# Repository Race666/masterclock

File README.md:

# Mutteruhrsteuerung

Firmware und Schaltungen zum Steuern von sog. Nebenuhren (z.B. Bahnhofsuhren)

Dokumentation und Details auf [albert-hetzles.de](http://albert-hetzles.de/mutteruhr/index.shtml)

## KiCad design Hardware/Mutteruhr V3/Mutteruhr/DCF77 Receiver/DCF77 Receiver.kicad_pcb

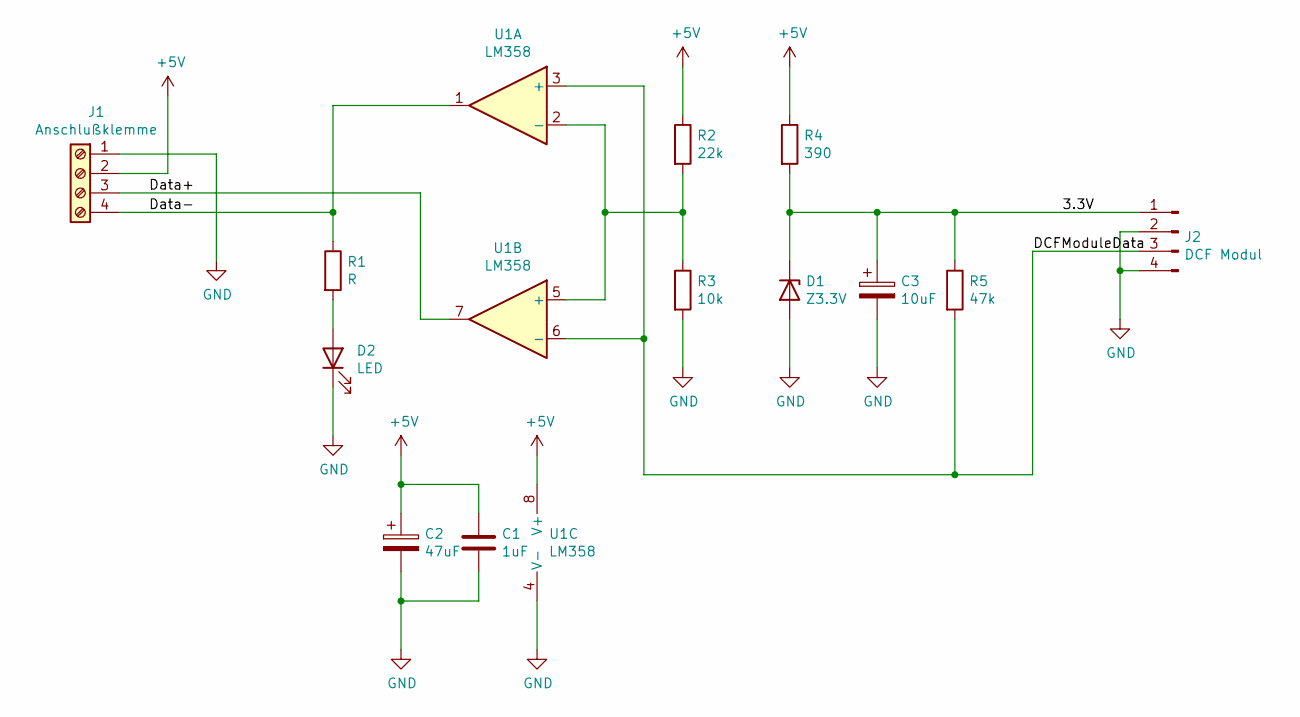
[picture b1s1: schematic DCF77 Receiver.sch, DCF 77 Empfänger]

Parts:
C1: 1uF; C_Rect_L7.0mm_W3.5mm_P5.00mm
C2: 47uF; CP_Radial_D6.3mm_P2.50mm
C3: 10uF; CP_Radial_D6.3mm_P2.50mm
D1: Z3.3V; D_DO-35_SOD27_P10.16mm_Horizontal
D2: LED; LED_D3.0mm
J1: Anschlußklemme; TerminalBlock_Phoenix_MKDS-3-4-5.08_1x04_P5.08mm_Horizontal
J2: DCF Modul; PinHeader_1x04_P2.54mm_Vertical
R1: R; R_Axial_DIN0207_L6.3mm_D2.5mm_P10.16mm_Horizontal
R2: 22k; R_Axial_DIN0207_L6.3mm_D2.5mm_P10.16mm_Horizontal
R3: 10k; R_Axial_DIN0207_L6.3mm_D2.5mm_P10.16mm_Horizontal
R4: 390; R_Axial_DIN0207_L6.3mm_D2.5mm_P10.16mm_Horizontal
R5: 47k; R_Axial_DIN0207_L6.3mm_D2.5mm_P10.16mm_Horizontal
U1: LM358; DIP-8_W7.62mm_LongPads

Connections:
+5V: C1.1, C2.1, J1.2, R2.1, R4.1, U1.8 (V+)
/3.3V: C3.1, D1.1 (K), J2.1, R4.2, R5.1
/DCFModuleData: J2.3, R5.2, U1.3 (+), U1.6 (-)
/Data+: J1.3, U1.7
/Data-: J1.4, R1.1, U1.1
GND: C1.2, C2.2, C3.2, D1.2 (A), D2.1 (K), J1.1, J2.2, J2.4, R3.2, U1.4 (V-)
unnamed: D2.2 (A), R1.2
unnamed: R2.2, R3.1, U1.2 (-), U1.5 (+)

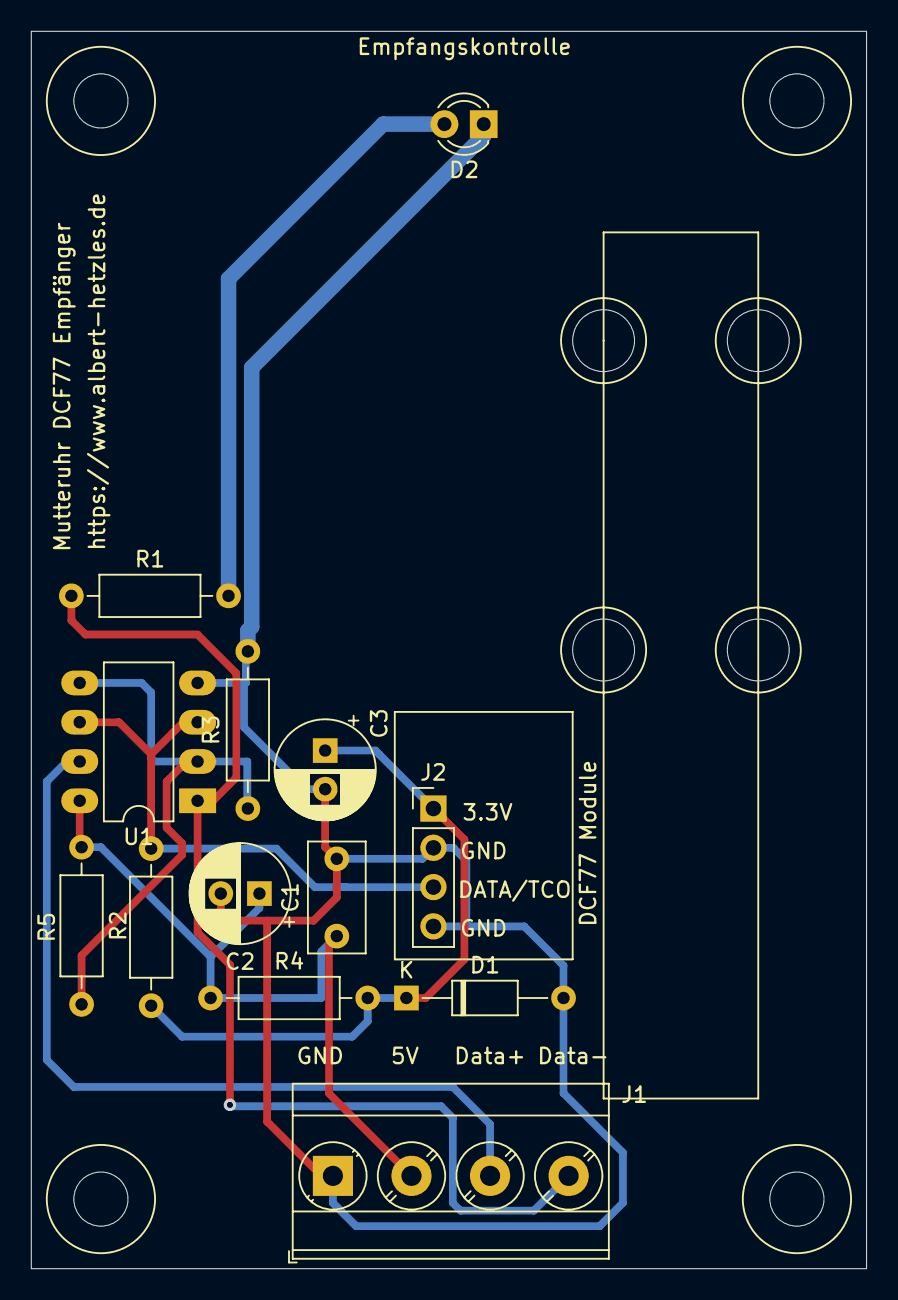
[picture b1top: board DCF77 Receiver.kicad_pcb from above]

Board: 2 copper layers, 54.0 x 80.0 mm, 13 parts (0 on the bottom side), 8 nets.

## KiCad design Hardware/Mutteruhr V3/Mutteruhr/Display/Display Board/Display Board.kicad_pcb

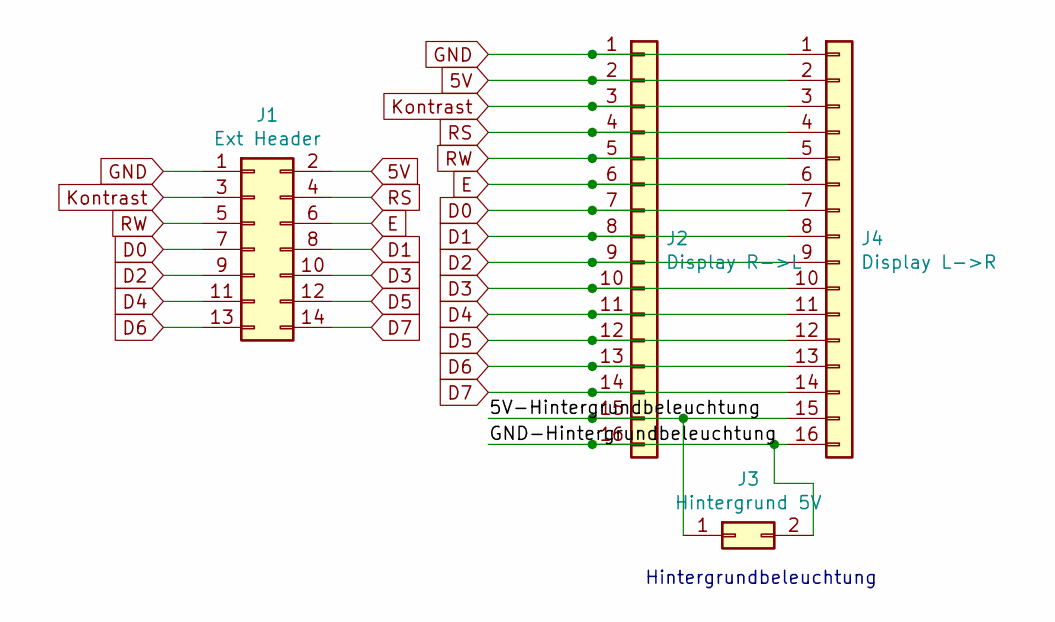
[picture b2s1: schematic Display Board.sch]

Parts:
J1: Ext Header; PinHeader_2x07_P2.54mm_Vertical
J2: Display R->L; PinHeader_1x16_P2.54mm_Vertical
J3: Hintergrund 5V; PinHeader_1x02_P2.54mm_Vertical
J4: Display L->R; PinHeader_1x16_P2.54mm_Vertical

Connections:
5V: J1.2, J2.2, J4.2
/5V-Hintergrundbeleuchtung: J2.15, J3.1, J4.15
/GND-Hintergrundbeleuchtung: J2.16, J3.2, J4.16
D0: J1.7, J2.7, J4.7
D1: J1.8, J2.8, J4.8
D2: J1.9, J2.9, J4.9
D3: J1.10, J2.10, J4.10
D4: J1.11, J2.11, J4.11
D5: J1.12, J2.12, J4.12
D6: J1.13, J2.13, J4.13
D7: J1.14, J2.14, J4.14
E: J1.6, J2.6, J4.6
GND: J1.1, J2.1, J4.1
Kontrast: J1.3, J2.3, J4.3
RS: J1.4, J2.4, J4.4
RW: J1.5, J2.5, J4.5

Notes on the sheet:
Hintergrundbeleuchtung

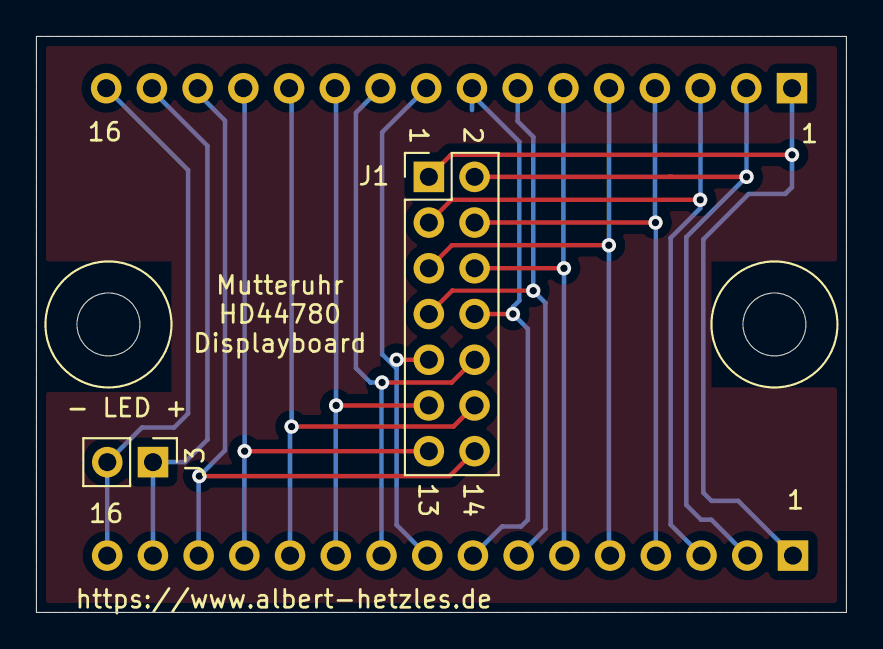
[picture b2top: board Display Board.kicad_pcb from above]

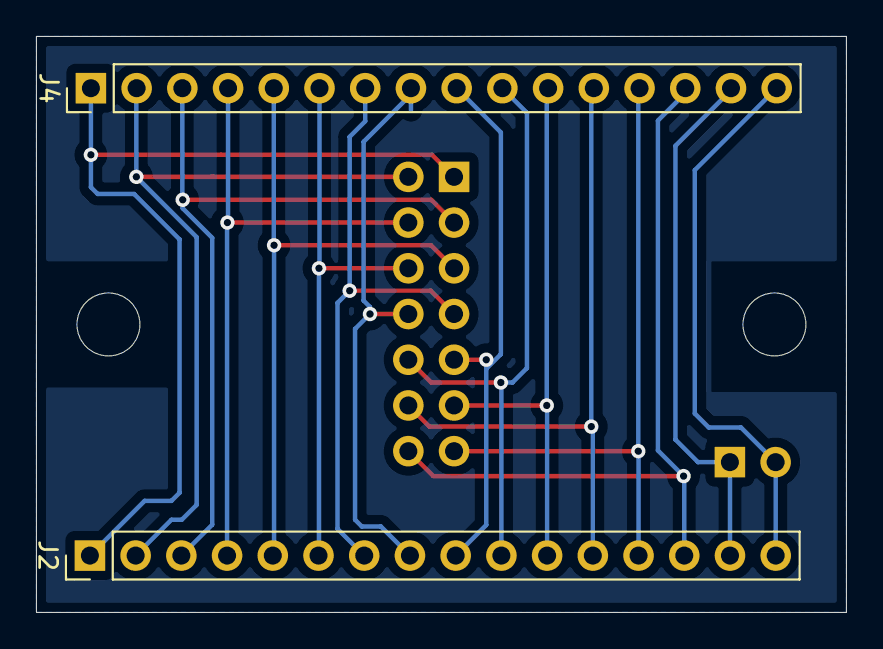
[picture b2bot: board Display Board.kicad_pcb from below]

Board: 2 copper layers, 45.0 x 32.0 mm, 4 parts (2 on the bottom side), 16 nets.

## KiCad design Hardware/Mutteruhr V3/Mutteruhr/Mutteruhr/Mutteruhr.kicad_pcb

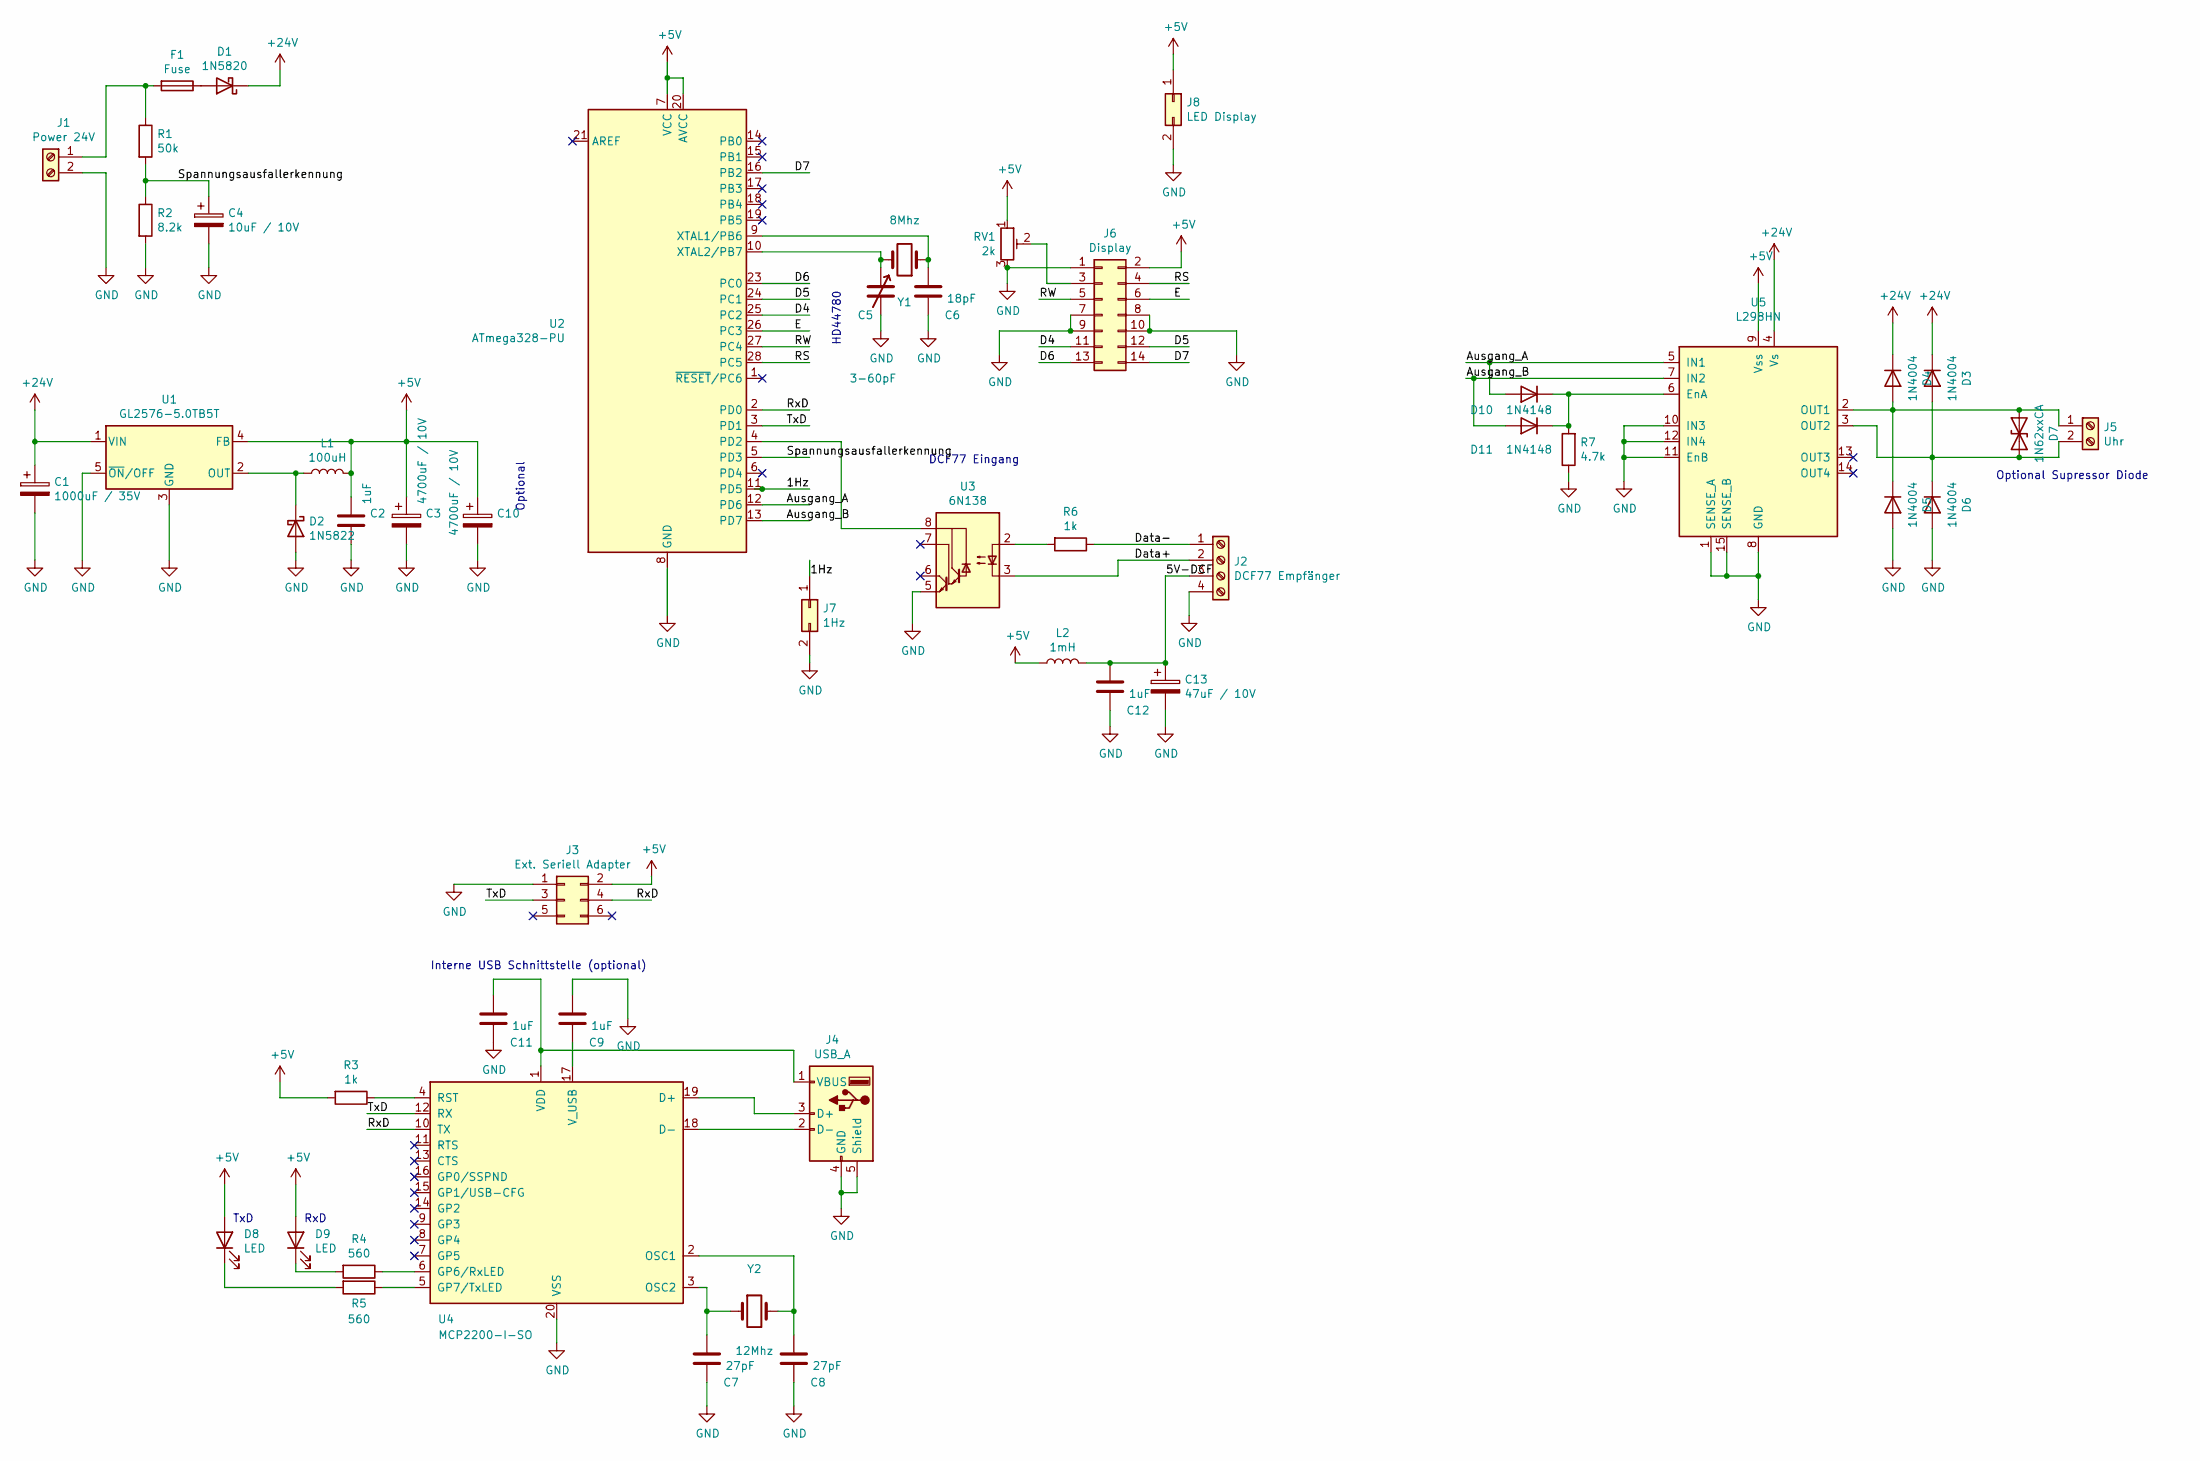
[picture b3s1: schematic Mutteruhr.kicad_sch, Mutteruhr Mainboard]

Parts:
C1: 1000uF / 35V; CP_Radial_D8.0mm_P5.00mm
C2, C9, C11, C12: 1uF; C_Rect_L7.0mm_W6.0mm_P5.00mm
C3, C10: 4700uF / 10V; CP_Radial_D10.0mm_P7.50mm
C4: 10uF / 10V; CP_Radial_D5.0mm_P2.50mm
C5: 3-60pF; C_Disc_D7.5mm_W5.0mm_P5.00mm
C6: 18pF; C_Disc_D3.0mm_W2.0mm_P2.50mm
C7, C8: 27pF; C_Disc_D3.0mm_W2.0mm_P2.50mm
C13: 47uF / 10V; CP_Radial_Tantal_D4.5mm_P2.50mm
D1: 1N5820; D_DO-41_SOD81_P10.16mm_Horizontal
D2: 1N5822; D_DO-41_SOD81_P10.16mm_Horizontal
D3, D4, D5, D6: 1N4004; D_DO-41_SOD81_P10.16mm_Horizontal
D7: 1N62xxCA; D_DO-41_SOD81_P10.16mm_Horizontal
D8, D9: LED; LED_D3.0mm_FlatTop
D10, D11: 1N4148; D_DO-35_SOD27_P7.62mm_Horizontal
F1: Fuse; Fuse_Bourns_MF-RHT500
J1: Power 24V; TerminalBlock_Phoenix_MKDS-1,5-2-5.08_1x02_P5.08mm_Horizont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
J2: DCF77 Empfänger; TerminalBlock_Phoenix_MKDS-1,5-4-5.08_1x04_P5.08mm_Horizont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
J3: Ext. Seriell Adapter; PinHeader_2x03_P2.54mm_Vertical
J4: USB_A; USB_B_OST_USB-B1HSxx_Horizontal
J5: Uhr; TerminalBlock_Phoenix_MKDS-1,5-2-5.08_1x02_P5.08mm_Horizont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
J6: Display; PinHeader_2x07_P2.54mm_Vertical
J7: 1Hz; PinHeader_1x02_P2.54mm_Vertical
J8: LED Display; PinHeader_1x02_P2.54mm_Vertical
L1: 100uH; L_Radial_D8.7mm_P5.00mm_Fastron_07HCP
L2: 1mH; L_Radial_D8.7mm_P5.00mm_Fastron_07HCP
R1: 50k; R_Axial_DIN0207_L6.3mm_D2.5mm_P10.16mm_Horizontal
R2: 8.2k; R_Axial_DIN0207_L6.3mm_D2.5mm_P10.16mm_Horizontal
R3, R6: 1k; R_Axial_DIN0207_L6.3mm_D2.5mm_P10.16mm_Horizontal
R4, R5: 560; R_Axial_DIN0204_L3.6mm_D1.6mm_P2.54mm_Vertical
R7: 4.7k; R_Axial_DIN0207_L6.3mm_D2.5mm_P10.16mm_Horizontal
RV1: 2k; Potentiometer_ACP_CA6-H2,5_Horizontal
U1: GL2576-5.0TB5T; TO-220-5_Vertical
U2: ATmega328-PU; DIP-28_W7.62mm
U3: 6N138; DIP-8_W7.62mm_LongPads
U4: MCP2200-I-SO; SOIC-20W_7.5x12.8mm_P1.27mm
U5: L298HN; TO-220-15_P2.54x2.54mm_StaggerOdd_Lead4.58mm_Vertical
Y1: 8Mhz; Crystal_HC49-U_Vertical
Y2: 12Mhz; Crystal_HC49-U_Vertical

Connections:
+5V: C2.1, C3.1, C10.1, D8.2 (A), D9.2 (A), J3.2, J6.2, J8.1, L1.2, L2.1, R3.2, RV1.1, U1.4 (FB), U2.7 (VCC), U2.20 (AVCC), U5.9 (Vss)
+24V: C1.1, D1.1 (K), D3.1 (K), D4.1 (K), U1.1 (VIN), U5.4 (Vs)
/1Hz: J7.1, U2.11 (PD5)
/5V-DCF: C12.1, C13.1, J2.3, L2.2
/Ausgang_A: D10.2 (A), U2.12 (PD6), U5.5 (IN1)
/Ausgang_B: D11.2 (A), U2.13 (PD7), U5.7 (IN2)
/D4: J6.11, U2.25 (PC2)
/D5: J6.12, U2.24 (PC1)
/D6: J6.13, U2.23 (PC0)
/D7: J6.14, U2.16 (PB2)
/Data+: J2.2, U3.3 (C2)
/Data-: J2.1, R6.1
/E: J6.6, U2.26 (PC3)
/RS: J6.4, U2.28 (PC5)
/RW: J6.5, U2.27 (PC4)
/RxD: J3.4, U2.2 (PD0), U4.10 (TX)
/Spannungsausfallerkennung: C4.1, R1.2, R2.1, U2.5 (PD3)
/TxD: J3.3, U2.3 (PD1), U4.12 (RX)
GND: C1.2, C2.2, C3.2, C4.2, C5.2, C6.2, C7.2, C8.2, C9.1, C10.2, C11.2, C12.2, C13.2, D2.2 (A), D5.2 (A), D6.2 (A), J1.2, J2.4, J3.1, J4.4 (GND), J4.5 (Shield), J6.1, J6.7, J6.8, J6.9, J6.10, J7.2, J8.2, R2.2, R7.1, RV1.3, U1.3 (GND), U1.5 (~ON/OFF), U2.8 (GND), U2.22 (GND), U3.5 (GND), U4.20 (VSS), U5.1 (SENSE_A), U5.8 (GND), U5.10 (IN3), U5.11 (EnB), U5.12 (IN4), U5.15 (SENSE_B)
unnamed: C5.1, U2.10 (XTAL2/PB7), Y1.2
unnamed: C6.1, U2.9 (XTAL1/PB6), Y1.1
unnamed: C7.1, U4.3 (OSC2), Y2.1
unnamed: C8.1, U4.2 (OSC1), Y2.2
unnamed: C9.2, U4.17 (V_USB)
unnamed: C11.1, J4.1 (VBUS), U4.1 (VDD)
unnamed: D1.2 (A), F1.1
unnamed: D2.1 (K), L1.1, U1.2 (OUT)
unnamed: D3.2 (A), D6.1 (K), D7.2 (A2), J5.2, U5.3 (OUT2)
unnamed: D4.2 (A), D5.1 (K), D7.1 (A1), J5.1, U5.2 (OUT1)
unnamed: D8.1 (K), R5.2
unnamed: D9.1 (K), R4.2
unnamed: D10.1 (K), D11.1 (K), R7.2, U5.6 (EnA)
unnamed: F1.2, J1.1, R1.1
unnamed: J4.2 (D-), U4.18 (D-)
unnamed: J4.3 (D+), U4.19 (D+)
unnamed: J6.3, RV1.2
unnamed: R3.1, U4.4 (RST)
unnamed: R4.1, U4.6 (GP6/RxLED)
unnamed: R5.1, U4.5 (GP7/TxLED)
unnamed: R6.2, U3.2 (C1)
unnamed: U2.4 (PD2), U3.8 (VCC)

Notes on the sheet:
RxD
Optional
Optional Supressor Diode
Interne USB Schnittstelle (optional)
HD44780
TxD
DCF77 Eingang

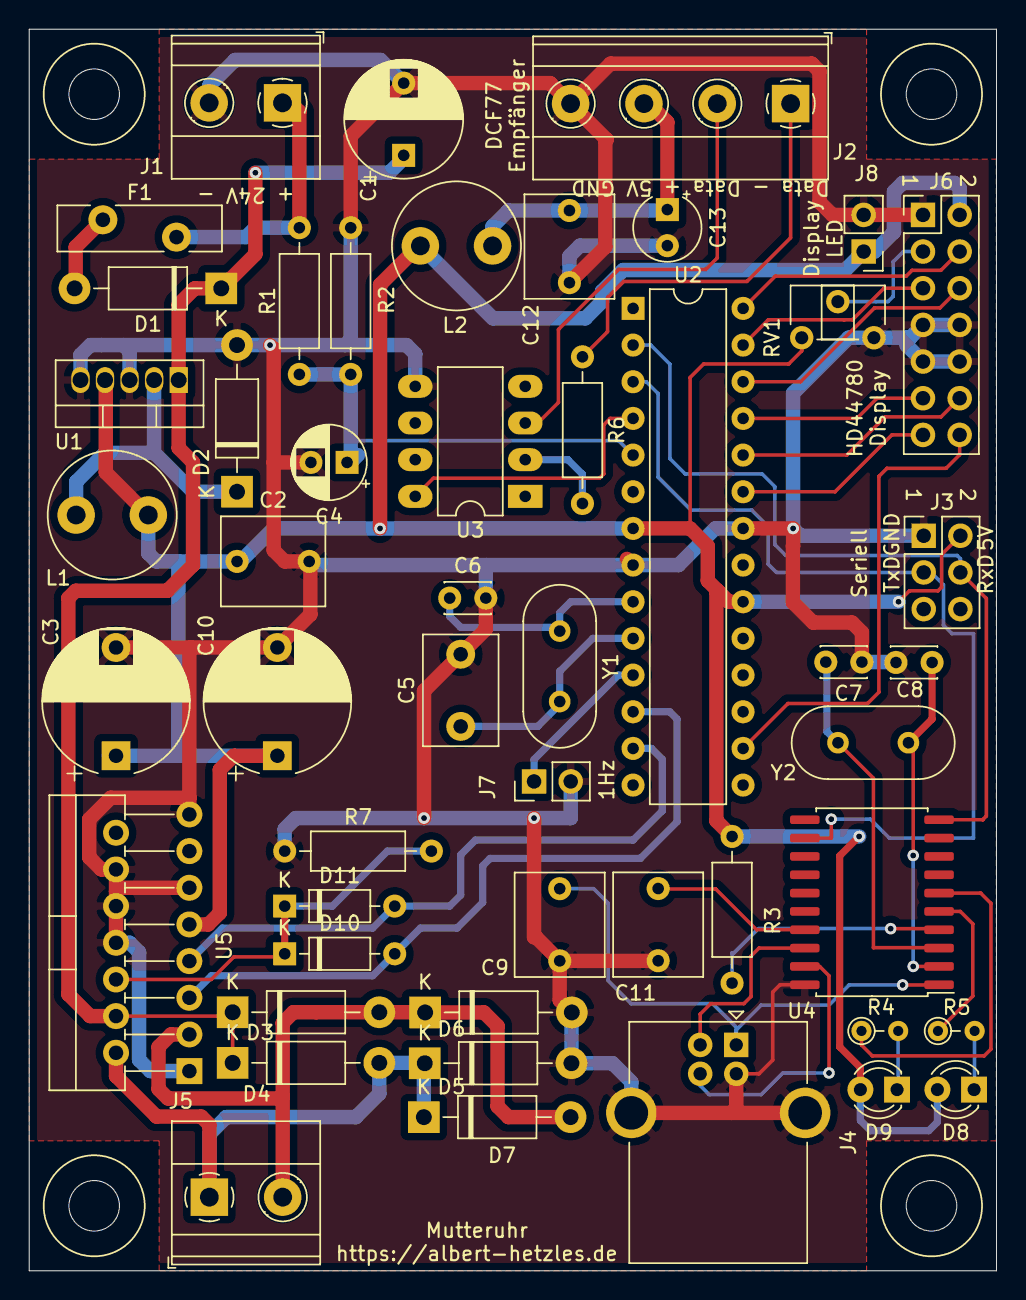
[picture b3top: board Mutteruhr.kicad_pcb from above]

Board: 2 copper layers, 67.0 x 86.0 mm, 50 parts (0 on the bottom side), 41 nets.

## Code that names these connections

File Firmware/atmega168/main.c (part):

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V1.05	  06.12.2010 michael@albert-hetzles.de Bug im  Protokoll gd7 behoben		
V1.06b2   25.10.2011 michael@albert-hetzles.de Trotz bDCF77=false wurde syncronisiert		
          20.12.2012 michael@albert-hetzles.de Peridodenzeit der Impulse beim synchronieren änderbar, default 1sec	
V1.06b4	  24.02.2013 michael@albert-hetzles.de Bug!!! Inkonsitenz Schaltplan und Programm OUTPUT_PULSE_EVEN PB0 -> PD6	   
V1.07	  06.03.2013 michael@albert-hetzles.de 1.07=1.06b4	
V1.08b1   01.03.2014 michael@albert-hetzles.de Bug in fInitLEDIOPorts Zeile 1573 	PORTD -> PORTC geändert
V1.08     22.06.2014 michael@albert-hetzles.de V1.08b1 -> V1.08
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// Max Pulsweite
#define MAX_PULSE_WIDTH_IN100MS 8
// Ausgang ungerade Minute
#define OUTPUT_PULSE_ODD PD7
// Ausgang gerade Minute
#define OUTPUT_PULSE_EVEN PD6
// Ausgang gerade Minute an
#define SET_PULSE_ODD {PORTD|=(1<<OUTPUT_PULSE_ODD);}
// Ausgang ungerade Minute an
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#define RESET_PULSE_EVEN {PORTD&=~(1<<OUTPUT_PULSE_EVEN);}

// Eingang für die Netzspannungsausfallerkennung
#define POWER_SUPPLY_ACTIVE_PIN PD3
// Macro zur Abfrage Netzspannungsausfallerkennung
#define POWER_SUPPLY_ACTIVE ((PIND) & (1<<POWER_SUPPLY_ACTIVE_PIN))
// Eingang für die LCD Display Abschaltung
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

// 1HZ Blink Ausgang
#define PIN_1HZ_BLINK PD5

// Ausgänge für LED's definieren
// Ausgang wenn DCF77 Daten empfangen werden
// Blinken=warte auf Daten, leuchten=Empfange Daten, aus=DCF77 Off
// Uhr syncronisiert
#define PIN_CLOCK_IS_SYNCING PC5
// DCF77 Health Status Leuchtet=DCF77 letzter DCF77 Empfang <1h; blinkt=DCF77 letzter DCF77 Empfang <24h;aus DCF77 letzter DCF77 Empfang >24h 
#define PIN_LED_DCF77_HEALTH_STATE PC4
// Gültiges DCF77 Paket empfangen
#define PIN_LED_DCF77_RETURN_STATE_OK PC3
// Ungültiges DCF77 Paket empfangen
#define PIN_LED_DCF77_RETURN_STATE_ERROR PC2
// Empfangsstatus blink=warte auf Daten, leuchtet=Empfange Daten
#define PIN_LED_DCF77_CURRENT_STATUS PC1



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#define DCF_PULSE_AND_PAUSE_CYCLE_SUM_MAX 8212
// Zeit für die die DCF Daten gültig sind
#define DCF77_IS_VALID_FOR_SECONDS 59
// EIngangspin für das DCF77 Signal, ISR0, PD2
#define DCF77_INPUT_PIN PD2
// Pegel für DCF In
#define HIGH 1
#define LOW 0
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	// EICRA |= (1<<ISC11);
	// ISR1 Steigende/Fallende Flanke
	EICRA |= (1<<ISC10);
	// Interrupt 1 (PD3)
	EIMSK |= (1<<INT1);
}
static void fInitLEDIOPorts(void){
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	// EICRA |= (1<<ISC01);
	//Steigende Flanke
	// EICRA |= (1<<ISC01) | (1<<ISC00);
	// Interrupt 0 (PD2)
	EIMSK |= (1<<INT0);
	// oder GICR |= (1<<INT0);
	tDCF77DateTime.iDCF77Status=DCF77_WAIT_FOR_SYNCING;
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
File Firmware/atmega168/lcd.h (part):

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#define LCD_DATA1_PORT   PORTC     /**< port for 4bit data bit 1 */
#define LCD_DATA2_PORT   PORTC     /**< port for 4bit data bit 2 */
#define LCD_DATA3_PORT   PORTB     /**< port for 4bit data bit 3 */
#define LCD_DATA0_PIN    PC2            /**< pin for 4bit data bit 0  */
#define LCD_DATA1_PIN    PC1            /**< pin for 4bit data bit 1  */
#define LCD_DATA2_PIN    PC0            /**< pin for 4bit data bit 2  */
#define LCD_DATA3_PIN    PB2            /**< pin for 4bit data bit 3  */
#define LCD_RS_PORT      PORTC     /**< port for RS line         */
#define LCD_RS_PIN       PC5            /**< pin  for RS line         */
#define LCD_RW_PORT      PORTC     /**< port for RW line         */
#define LCD_RW_PIN       PC4            /**< pin  for RW line         */
#define LCD_E_PORT       PORTC     /**< port for Enable line     */
#define LCD_E_PIN        PC3            /**< pin  for Enable line     */

#elif defined(__AVR_AT90S4414__) || defined(__AVR_AT90S8515__) || defined(__AVR_ATmega64__) || \
      defined(__AVR_ATmega8515__)|| defined(__AVR_ATmega103__) || defined(__AVR_ATmega128__) || \
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
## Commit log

2010-03-06 v1.07
2010-07-09 v1.00
2010-08-09 v1.01
2010-08-27 v1.02
2010-08-31 v1.03
2010-11-23 v1.04
2010-12-06 v1.05
2013-02-24 v1.06b4
2014-06-22 v1.08
2014-09-16 v1.09
2016-11-09 Hardware V1.0, V2.0, V2.1 hinzugefuegt
2018-10-23 Branch linux-build. Umstellung WinAVR -> Linux (Debian)
2019-09-18 Diverse bool variablen nach stdbool migiert. DCF77 Debug variablen hinzugefuegt
2019-09-18 dbgdcf command nach _dbgdcf umgestellt
2019-09-18 iMenuPosition -> iShellPosition
2019-09-18 Umstellung Shell Position auf Konstanten. 0 -> SHELL_MENU_PROMPT
2019-09-18 Umstellung Shell Position auf Konstanten. 1 -> SHELL_MENU_SMT
2019-09-18 Umstellung Shell Position auf Konstanten. 2 -> SHELL_MENU_NST
2019-09-18 Umstellung Shell Position auf Konstanten. 3 -> SHELL_MENU_AST
2019-09-18 Umstellung Shell Position auf Konstanten. 4 -> SHELL_MENU_DCF_ON_OFF
2019-09-18 Umstellung Shell Position auf Konstanten. 5 -> SHELL_MENU_PST
2019-09-18 Umstellung Shell Position auf Konstanten. 6 -> SHELL_MENU_SSM
2019-09-18 Umstellung Shell Position auf Konstanten. 7 -> SHELL_MENU_SPW
2019-09-18 Umstellung auf Konstanten fuer iDisplayPage. 0->DISPLAY_PAGE_TIME_ON_SLAVES,1->DISPLAY_PAGE_CLOCK_IS_SYNCING
2019-09-18 Umstellung auf Konstanten fuer iDisplayPage. 2->DISPLAY_PAGE_DCF_OP_MODE, 3->DISPLAY_PAGE_DCF_STATUS, 4->DISPLAY_PAGE_DCF_LAST_RESULT, 5->DISPLAY_PAGE_DCF_RECEIVE_BIT_STATE
2019-09-18 Umstellung auf Konstanten fuer iDisplayPage. 6->DISPLAY_PAGE_DCF_SHOW_DATE_TIME, 7->DISPLAY_PAGE_CLOCK_SYNC_MODE_12H_24H, 8->DISPLAY_PAGE_INVALID
2019-09-18 Display update geaendert von 1sec auf 0.5sec. Displaypage fuer DCF Debug aktiviert
2019-09-18 Ueberpruefung ob Display Page gueltig ist von main nach fExecuteEverySecond umgezogen
2019-09-18 Neue Funktion fGetLeftAlignedFilledUpString, Preproc DCF_DEBUG vervollstaendigt
2019-09-19 Neue Funktion fGetLeftRightAlignedFilledUpString, 2. sTemp Variable -> sTemp1 und sTemp2. Ausgabe von DISPLAY_PAGE_DCF_DEBUG_TIMING ergaenzt
2019-09-20 Ausgabe ueber Display eingebaut
2020-07-01 Fehler an USB MCP2200 VDD gefixt. Verbindung Pin 1 - 17 getrennt
2020-07-01 Fehler an USB MCP2200 VDD gefixt. Verbindung Pin 1 - 17 getrennt: Branch linux-build
2020-09-30 Sekunden Counter mit DCF synchronsieren
2020-09-30 Precompiled maix.hex main.epp
2023-12-17 Hardware Revision V3
